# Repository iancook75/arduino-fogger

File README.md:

arduino-fogger
==============

Arduino Frog Tank Fogging Apparatus

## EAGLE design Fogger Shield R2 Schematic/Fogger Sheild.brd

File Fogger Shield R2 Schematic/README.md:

Use Eagle To Open
http://www.cadsoftusa.com/download-eagle/?language=en

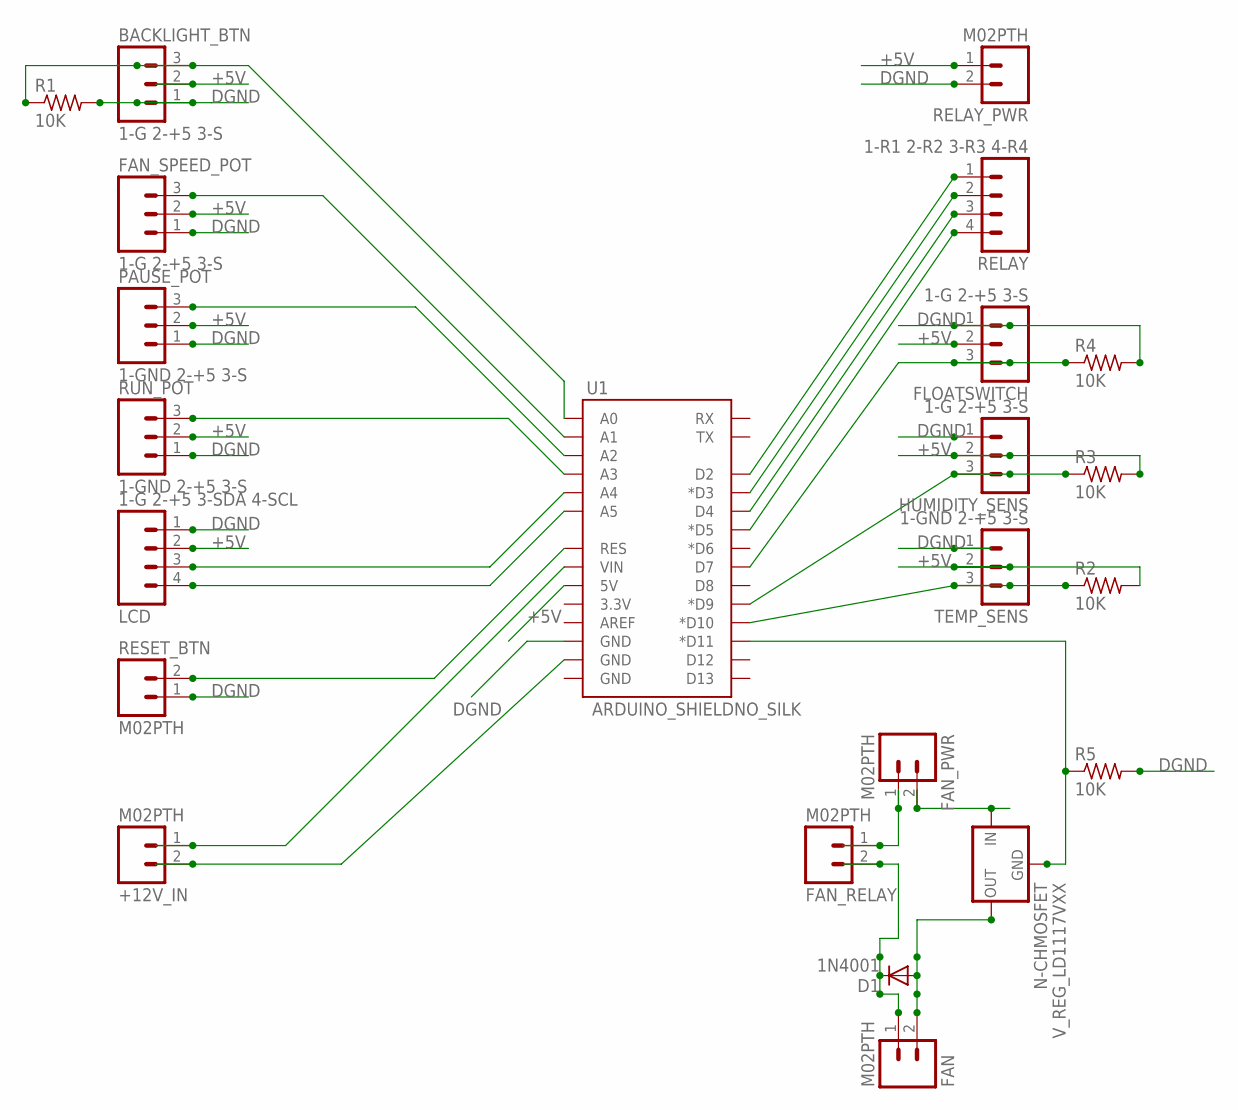
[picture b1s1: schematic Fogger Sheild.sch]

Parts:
+12V_IN: M02PTH; 1X02
BACKLIGHT_BTN: 1-G 2-+5 3-S; 1X03_LOCK
D1: 1N4001; DIODE-1N4001
FAN: M02PTH; 1X02
FAN_PWR: M02PTH; 1X02
FAN_RELAY: M02PTH; 1X02
FAN_SPEED_POT: 1-G 2-+5 3-S; 1X03
FLOATSWITCH: 1-G 2-+5 3-S; 1X03_LOCK
HUMIDITY_SENS: 1-G 2-+5 3-S; 1X03
LCD: 1-G 2-+5 3-SDA 4-SCL; 1X04
N-CHMOSFET: V_REG_LD1117VXX; 78XXL
PAUSE_POT: 1-GND 2-+5 3-S; 1X03_LOCK
R1, R4: 10K; 0204/5
R2, R3, R5: 10K; 0204V
RELAY: 1-R1 2-R2 3-R3 4-R4; 1X04
RELAY_PWR: M02PTH; 1X02
RESET_BTN: M02PTH; 1X02
RUN_POT: 1-GND 2-+5 3-S; 1X03
TEMP_SENS: 1-GND 2-+5 3-S; 1X03_LOCK
U1: ARDUINO_SHIELDNO_SILK; DUEMILANOVE_VIAS

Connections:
+5V: BACKLIGHT_BTN.2, FAN_SPEED_POT.2, FLOATSWITCH.2, HUMIDITY_SENS.2, LCD.2, PAUSE_POT.2, R2.2, R3.2, RELAY_PWR.1, RUN_POT.2, TEMP_SENS.2, U1.5V
DGND: BACKLIGHT_BTN.1, FAN_SPEED_POT.1, FLOATSWITCH.1, HUMIDITY_SENS.1, LCD.1, PAUSE_POT.1, R1.2, R4.2, R5.2, RELAY_PWR.2, RESET_BTN.1, RUN_POT.1, TEMP_SENS.1, U1.GND@2 (GND)
unnamed: RELAY.4, U1.D5 (*D5)
unnamed: RELAY.3, U1.D4
unnamed: RELAY.2, U1.D3 (*D3)
unnamed: RELAY.1, U1.D2
unnamed: LCD.3, U1.A4
unnamed: LCD.4, U1.A5
unnamed: RUN_POT.3, U1.A3
unnamed: PAUSE_POT.3, U1.A2
unnamed: FAN_SPEED_POT.3, U1.A1
unnamed: +12V_IN.2, U1.GND@1 (GND)
unnamed: RESET_BTN.2, U1.RES
unnamed: +12V_IN.1, U1.VIN
unnamed: BACKLIGHT_BTN.3, R1.1, U1.A0
unnamed: FLOATSWITCH.3, R4.1, U1.D7
unnamed: HUMIDITY_SENS.3, R3.1, U1.D9 (*D9)
unnamed: R2.1, TEMP_SENS.3, U1.D10 (*D10)
unnamed: N-CHMOSFET.IN (GND), R5.1, U1.D11 (*D11)
unnamed: FAN_PWR.2, N-CHMOSFET.OUT (IN)
unnamed: D1.A, FAN.2, N-CHMOSFET.GND (OUT)
unnamed: D1.C, FAN.1, FAN_RELAY.2
unnamed: FAN_PWR.1, FAN_RELAY.1

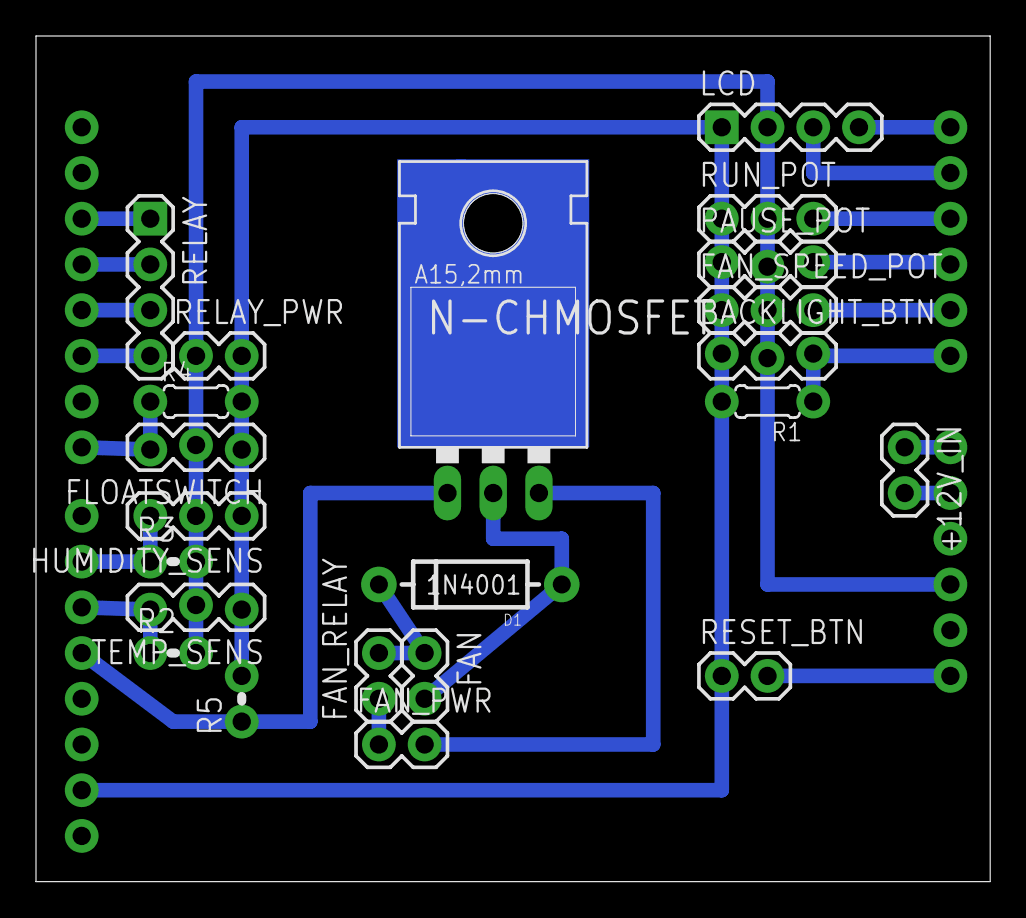
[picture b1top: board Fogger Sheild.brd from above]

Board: 2 copper layers, 53.0 x 47.0 mm, 23 parts (0 on the bottom side), 23 nets.

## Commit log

2013-06-10 Base Libraries and Frog Fogger Source
2013-06-10 Frog Fogger Shield Schematics for hardware R1 and R2
2013-06-11 Parts Lists and Initial Frogduino Schematic
2013-06-12 Updated Parts List
2013-06-12 Updated Files
2013-06-18 Updated Schematic
2013-06-20 Updated Schematics
2013-07-12 Updated Things

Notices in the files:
parts and their libraries:
SparkFun-Boards: Licensing: CC v3.0 Share-Alike You are welcome to use this library for commercial purposes.
